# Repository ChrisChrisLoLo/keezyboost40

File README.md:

# keezyboost40

A 4x10 low profile ortholinear keyboard with an lcd screen in the center. Uses the Raspberry Pi Pico as well as firmware written in Rust (though QMK works too*)

## Features
- Low Profile
    - Keyboard is around 16.5mm thick, keys and keycaps included
- 1.8" LCD Screen
    - Ample real estate for animations, UI, games(?), etc.
- Uses the Raspberry Pi Pico
    - 2MB of flash storage
        - Lots of room for programming with MicroPython, or room for graphics and code
- Parts readily available
    - Only SMD parts required are diodes and kailh choc hotswap sockets
- Supports QMK or Rust firmware
    - QMK hex can be found in firmware file
    - Uses Keyberon as the firmware base, allowing for a "modular" firmware that can easily be built upon
    - More details can be found in DESIGN.md

Display demo here:

## Status
Prototypes are functional, though firmware is still WIP! v0.0 needs a jumper cable from the Pico to the reset pin in the TFT, but works perfectly fine with the Raspberry Pi Pico aside from that. v0.1 fixes this issue (currently in the `master` branch), though hasn't been produced and tested yet.

I need to fix a bug with the animation slowing down, though I suspect it'll mostly involve tinkering with RTOS timings

## PCB
You can generate the gerbers from source in the `pcb` directory, and send off imediately to PCBWay or the like. [PCBWay](https://www.pcbway.com/) has helped sponsor this project, and has provided a fast, easy service while ordering from them. I was also suprised how well my board came out desipte being quite oddly shaped, so I recommend checking them out for your next project!

## BOM
The following is the materials you will want/need to make your own keezyboost40. Note that anything amount after a `+` denotes the rough amount of spares you may want to have when ordering the parts. Anything involving the acrylic screen is optional. Even the LCD is optional if you prefer more of a lumberjack-y vibe :)
|Part|Count|Notes
|---|---|---|
|PCB|  1|   duh|
|Kailh Choc Hotswap Switches| 40+10| |
|LL4148 SMD Diodes|  40+10| This board uses SMD diodes exclusively. I found though-hole diodes often easily slipped around in a way such that the board was no longer able to fit inside the case|
|1.8" ST7735 TFT|  1| Generally speaking, you want the one with the Red PCB. Do NOT use the one from Adafruit, as the pin order on that one is different|
|Raspberry Pi Pico|  1| Try to get the original or a _very_ similar clone with castellated pins. From casual testing, other RP2040 boards may not work (for example, the Pico clones from WeAct can't seem to properly drive the LCD with 3.3V logic)|
|Rubber Feet|  6+2| Any should generally work, though I'm using ~2.5mm thick ones, as they give more space for screw heads, as well as the magnetic connector I'm using|
|3D Printed Case|  1| You could use PCB printing services like PCBWay to make one in resin, though I haven't confirmed if they'd be durable enough to survive in transit|
|M2 Nuts|  10+5| 6 nuts to hold the PCB to the case, and another 4 to hold the acrylic screen to the PCB. I'm using nylon nuts, though any should work. I recommend you grab this with a hex spacer kit, as you get all the M2 parts you need in a single purchase!|
|M2 8mm Double Female spacer|  4+2| Spacers to keep the acrylic from the pcb|
|M2 12mm Screw|  4+2| Screws for the acrylic screen|
|M2 6mm Screw|  6+3| Screws for the PCB and case. Be careful of the size of the screw head! the flatter the better!|
|Acrylic Screen|  1| You can cut one out using the svgs in the `outlines` folder|

## Design
See `DESIGN.md` for small insights about the design choices that went into this board. 

## Directory Structure
- `case`
    You can find the files you need in this folder to print out a case for the keyboard
- `drafts`
    Stores any KLE or intermediate information used in making the case
- `firmware`
    Used to store any firmware relating to the keyboard. Merges to the QMK repo planned.
- `outlines`
    Outlines used for the acrylic screen. Use these to cut your own!
- `pcb`
    Kicad project relating to the project

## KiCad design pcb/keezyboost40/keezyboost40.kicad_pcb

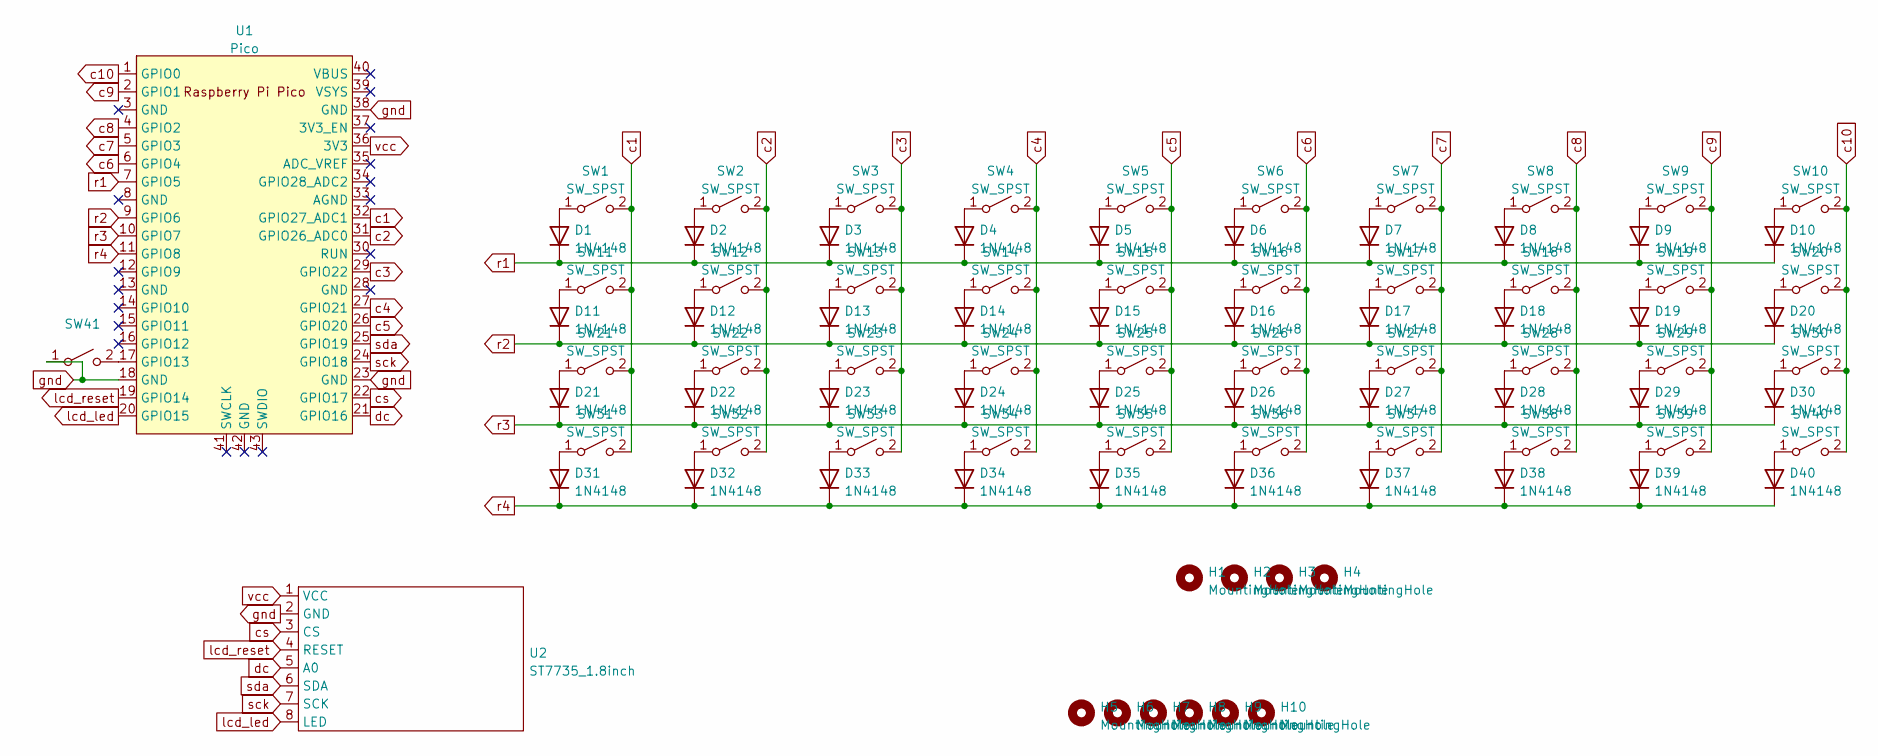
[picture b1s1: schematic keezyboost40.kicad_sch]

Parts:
D1, D2, D3, D4, D5, D6, D7, D8, D9, D10, D11, D12, D13, D14, D15, D16, D17, D18, D19, D20, D21, D22, D23, D24, D25, D26, D27, D28, D29, D30, D31, D32, D33, D34, D35, D36, D37, D38, D39, D40: 1N4148; D_SOD-123
H1, H2, H3, H4: MountingHole; MountingHole_2.2mm_M2_DIN965_Pad
H5, H6, H7, H8, H9, H10: MountingHole; MountingHole_2.2mm_M2
SW1, SW2, SW3, SW4, SW5, SW6, SW7, SW8, SW9, SW10, SW11, SW12, SW13, SW14, SW15, SW16, SW17, SW18, SW19, SW20, SW21, SW22, SW23, SW24, SW25, SW26, SW27, SW28, SW29, SW30, SW31, SW32, SW33, SW34, SW35, SW36, SW37, SW38, SW39, SW40: SW_SPST; Kailh_socket_PG1350
SW41: (no value)
U1: Pico; RPi_Pico_SMD_TH_OPEN
U2: ST7735_1.8inch

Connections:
unnamed: D1.2 (A), SW1.1 (A)
unnamed: D2.2 (A), SW2.1 (A)
unnamed: D3.2 (A), SW3.1 (A)
unnamed: D4.2 (A), SW4.1 (A)
unnamed: D5.2 (A), SW5.1 (A)
unnamed: D6.2 (A), SW6.1 (A)
unnamed: D7.2 (A), SW7.1 (A)
unnamed: D8.2 (A), SW8.1 (A)
unnamed: D9.2 (A), SW9.1 (A)
unnamed: D10.2 (A), SW10.1 (A)
unnamed: D11.2 (A), SW11.1 (A)
unnamed: D12.2 (A), SW12.1 (A)
unnamed: D13.2 (A), SW13.1 (A)
unnamed: D14.2 (A), SW14.1 (A)
unnamed: D15.2 (A), SW15.1 (A)
unnamed: D16.2 (A), SW16.1 (A)
unnamed: D17.2 (A), SW17.1 (A)
unnamed: D18.2 (A), SW18.1 (A)
unnamed: D19.2 (A), SW19.1 (A)
unnamed: D20.2 (A), SW20.1 (A)
unnamed: D21.2 (A), SW21.1 (A)
unnamed: D22.2 (A), SW22.1 (A)
unnamed: D23.2 (A), SW23.1 (A)
unnamed: D24.2 (A), SW24.1 (A)
unnamed: D25.2 (A), SW25.1 (A)
unnamed: D26.2 (A), SW26.1 (A)
unnamed: D27.2 (A), SW27.1 (A)
unnamed: D28.2 (A), SW28.1 (A)
unnamed: D29.2 (A), SW29.1 (A)
unnamed: D30.2 (A), SW30.1 (A)
unnamed: D31.2 (A), SW31.1 (A)
unnamed: D32.2 (A), SW32.1 (A)
unnamed: D33.2 (A), SW33.1 (A)
unnamed: D34.2 (A), SW34.1 (A)
unnamed: D35.2 (A), SW35.1 (A)
unnamed: D36.2 (A), SW36.1 (A)
unnamed: D37.2 (A), SW37.1 (A)
unnamed: D38.2 (A), SW38.1 (A)
unnamed: D39.2 (A), SW39.1 (A)
unnamed: D40.2 (A), SW40.1 (A)
unnamed: SW41.2 (B), U1.17 (GPIO13)
c1: SW1.2 (B), SW11.2 (B), SW21.2 (B), SW31.2 (B), U1.32 (GPIO27_ADC1)
c2: SW2.2 (B), SW12.2 (B), SW22.2 (B), SW32.2 (B), U1.31 (GPIO26_ADC0)
c3: SW3.2 (B), SW13.2 (B), SW23.2 (B), SW33.2 (B), U1.29 (GPIO22)
c4: SW4.2 (B), SW14.2 (B), SW24.2 (B), SW34.2 (B), U1.27 (GPIO21)
c5: SW5.2 (B), SW15.2 (B), SW25.2 (B), SW35.2 (B), U1.26 (GPIO20)
c6: SW6.2 (B), SW16.2 (B), SW26.2 (B), SW36.2 (B), U1.6 (GPIO4)
c7: SW7.2 (B), SW17.2 (B), SW27.2 (B), SW37.2 (B), U1.5 (GPIO3)
c8: SW8.2 (B), SW18.2 (B), SW28.2 (B), SW38.2 (B), U1.4 (GPIO2)
c9: SW9.2 (B), SW19.2 (B), SW29.2 (B), SW39.2 (B), U1.2 (GPIO1)
c10: SW10.2 (B), SW20.2 (B), SW30.2 (B), SW40.2 (B), U1.1 (GPIO0)
cs: U1.22 (GPIO17), U2.3 (CS)
dc: U1.21 (GPIO16), U2.5 (A0)
gnd: SW41.1 (A), U1.18 (GND), U1.23 (GND), U1.38 (GND), U2.2 (GND)
lcd_led: U1.20 (GPIO15), U2.8 (LED)
lcd_reset: U1.19 (GPIO14), U2.4 (RESET)
r1: D1.1 (K), D2.1 (K), D3.1 (K), D4.1 (K), D5.1 (K), D6.1 (K), D7.1 (K), D8.1 (K), D9.1 (K), D10.1 (K), U1.7 (GPIO5)
r2: D11.1 (K), D12.1 (K), D13.1 (K), D14.1 (K), D15.1 (K), D16.1 (K), D17.1 (K), D18.1 (K), D19.1 (K), D20.1 (K), U1.9 (GPIO6)
r3: D21.1 (K), D22.1 (K), D23.1 (K), D24.1 (K), D25.1 (K), D26.1 (K), D27.1 (K), D28.1 (K), D29.1 (K), D30.1 (K), U1.10 (GPIO7)
r4: D31.1 (K), D32.1 (K), D33.1 (K), D34.1 (K), D35.1 (K), D36.1 (K), D37.1 (K), D38.1 (K), D39.1 (K), D40.1 (K), U1.11 (GPIO8)
sck: U1.24 (GPIO18), U2.7 (SCK)
sda: U1.25 (GPIO19), U2.6 (SDA)
vcc: U1.36 (3V3), U2.1 (VCC)

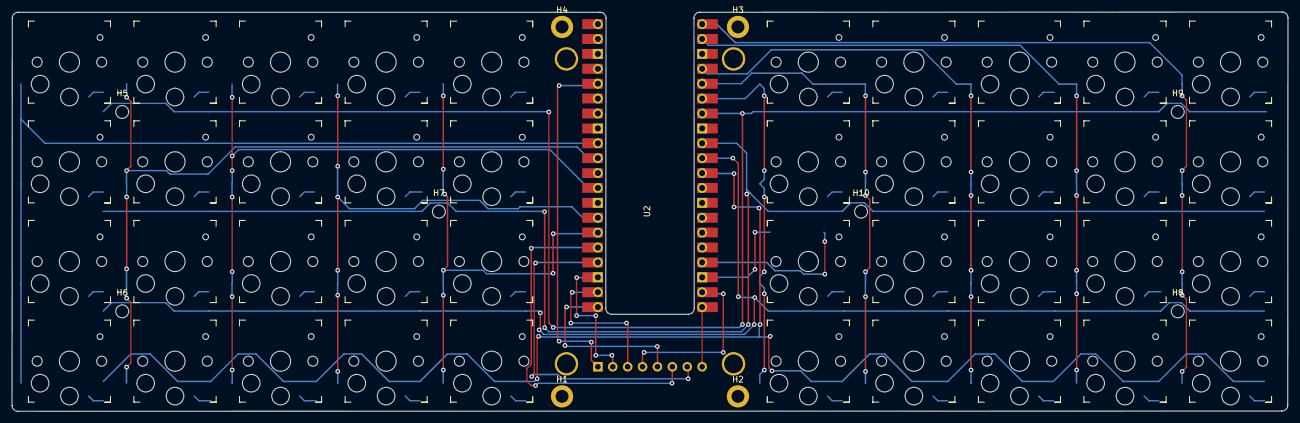
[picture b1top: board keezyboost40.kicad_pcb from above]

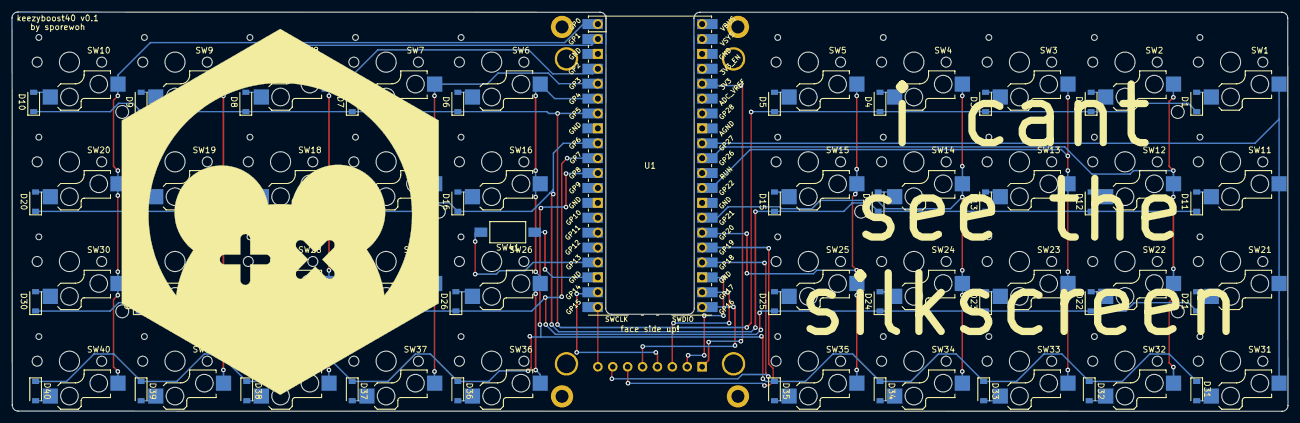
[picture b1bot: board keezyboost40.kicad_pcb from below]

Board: 2 copper layers, 217.6 x 68.1 mm, 93 parts (42 on the bottom side), 63 nets.

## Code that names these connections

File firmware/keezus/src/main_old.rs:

// Base taken from https://github.com/bschwind/key-ripper/blob/main/firmware/src/main.rs

#![no_main]
#![no_std]



use core::convert::Infallible;
use cortex_m::delay::Delay;
use defmt::{error, info};
use defmt_rtt as _;
use embedded_hal::{
    digital::v2::{InputPin, OutputPin},
    timer::CountDown,
};
use embedded_time::duration::Extensions;
// use panic_reset as _;
use panic_probe as _;
use rp2040_hal::{pac, usb::UsbBus, Clock, Watchdog};
use usb_device::{bus::UsbBusAllocator, device::UsbDeviceBuilder, prelude::UsbVidPid, UsbError};
use usbd_hid::{
    descriptor::KeyboardReport,
    hid_class::{
        HIDClass, HidClassSettings, HidCountryCode, HidProtocol, HidSubClass, ProtocolModeConfig,
    },
};

// lcd traits
use embedded_graphics::image::{Image, ImageRaw, ImageRawLE};
use embedded_graphics::prelude::*;
use embedded_graphics::pixelcolor::Rgb565;
use st7735_lcd;
use st7735_lcd::Orientation;
use embedded_time::rate::Hertz;

/// The linker will place this boot block at the start of our program image. We
/// need this to help the ROM bootloader get our code up and running.
#[link_section = ".boot2"]
#[used]
pub static BOOT2: [u8; 256] = rp2040_boot2::BOOT_LOADER_W25Q080;

mod hid_descriptor;
mod key_codes;
mod key_mapping;

const NUM_COLS: usize = 14;
const NUM_ROWS: usize = 6;

const EXTERNAL_CRYSTAL_FREQUENCY_HZ: u32 = 12_000_000;

#[defmt::panic_handler]
fn panic() -> ! {
    cortex_m::asm::udf()
}

#[cortex_m_rt::entry]
fn main() -> ! {
    info!("Start of main()");
    let mut pac = pac::Peripherals::take().unwrap();
    let core = pac::CorePeripherals::take().unwrap();

    let mut watchdog = Watchdog::new(pac.WATCHDOG);

    let clocks = rp2040_hal::clocks::init_clocks_and_plls(
        EXTERNAL_CRYSTAL_FREQUENCY_HZ,
        pac.XOSC,
        pac.CLOCKS,
        pac.PLL_SYS,
        pac.PLL_USB,
        &mut pac.RESETS,
        &mut watchdog,
    )
    .ok()
    .unwrap();

    // Setup USB
    let force_vbus_detect_bit = true;
    let usb_bus = UsbBus::new(
        pac.USBCTRL_REGS,
        pac.USBCTRL_DPRAM,
        clocks.usb_clock,
        force_vbus_detect_bit,
        &mut pac.RESETS,
    );

    let bus_allocator = UsbBusAllocator::new(usb_bus);

    // Note - Going lower than this requires switch debouncing.
    let poll_ms = 8;
    let mut hid_endpoint = HIDClass::new_with_settings(
        &bus_allocator,
        hid_descriptor::KEYBOARD_REPORT_DESCRIPTOR,
        poll_ms,
        HidClassSettings {
            subclass: HidSubClass::NoSubClass,
            protocol: HidProtocol::Keyboard,
            config: ProtocolModeConfig::ForceReport,
            // locale: HidCountryCode::NotSupported,
            locale: HidCountryCode::US,
        },
    );

    info!("USB initialized");

    // https://github.com/obdev/v-usb/blob/7a28fdc685952412dad2b8842429127bc1cf9fa7/usbdrv/USB-IDs-for-free.txt#L128
    let mut keyboard_usb_device = UsbDeviceBuilder::new(&bus_allocator, UsbVidPid(0x16c0, 0x27db))
        .manufacturer("bschwind")
        .product("key ripper")
        .build();

    // Get the GPIO peripherals.
    let sio = rp2040_hal::Sio::new(pac.SIO);

    let pins =
        rp2040_hal::gpio::Pins::new(pac.IO_BANK0, pac.PADS_BANK0, sio.gpio_bank0, &mut pac.RESETS);

    // Set up keyboard matrix pins.
    let rows: &[&dyn InputPin<Error = Infallible>] = &[
        &pins.gpio5.into_pull_down_input(),
        &pins.gpio6.into_pull_down_input(),
        &pins.gpio7.into_pull_down_input(),
        &pins.gpio8.into_pull_down_input(),
    ];

    let cols: &mut [&mut dyn OutputPin<Error = Infallible>] = &mut [
        &mut pins.gpio27.into_push_pull_output(),
        &mut pins.gpio26.into_push_pull_output(),
        &mut pins.gpio22.into_push_pull_output(),
        &mut pins.gpio21.into_push_pull_output(),
        &mut pins.gpio20.into_push_pull_output(),
        &mut pins.gpio4.into_push_pull_output(),
        &mut pins.gpio3.into_push_pull_output(),
        &mut pins.gpio2.into_push_pull_output(),
        &mut pins.gpio1.into_push_pull_output(),
        &mut pins.gpio0.into_push_pull_output(),
    ];

    // Timer-based resources.
    let mut delay = cortex_m::delay::Delay::new(core.SYST, clocks.system_clock.freq().0);

    let timer = rp2040_hal::Timer::new(pac.TIMER, &mut pac.RESETS);
    let mut scan_countdown = timer.count_down();

    // Start on a 500ms countdown so the USB endpoint writes don't block.
    scan_countdown.start(500.milliseconds());

    //// Start the TFT screen

    // These are implicitly used by the spi driver if they are in the correct mode
    let _spi_sclk = pins.gpio18.into_mode::<rp2040_hal::gpio::FunctionSpi>();
    let _spi_mosi = pins.gpio19.into_mode::<rp2040_hal::gpio::FunctionSpi>();
    //let _spi_miso = pins.gpio4.into_mode::<rp2040_hal::gpio::FunctionSpi>();
    let spi = rp2040_hal::Spi::<_, _, 8>::new(pac.SPI0);

    let mut lcd_led = pins.gpio15.into_push_pull_output();
    let dc = pins.gpio16.into_push_pull_output();
    let rst = pins.gpio14.into_push_pull_output();

    // Exchange the uninitialised SPI driver for an initialised one
    let spi = spi.init(
        &mut pac.RESETS,
        clocks.peripheral_clock.freq(),
        Hertz::new(16_000_000u32),
        &embedded_hal::spi::MODE_0,
    );


    let mut disp = st7735_lcd::ST7735::new(spi, dc, rst, true, false, 128, 160);

    disp.init(&mut delay).unwrap();
    disp.set_orientation(&Orientation::PortraitSwapped).unwrap();
    disp.clear(Rgb565::BLACK).unwrap();
    disp.set_offset(0, 25);

    let image_raw: ImageRawLE<Rgb565> =
        ImageRaw::new(include_bytes!("../assets/ferris.raw"), 86);

    let image: Image<_> = Image::new(&image_raw, Point::new(24, 28));

    image.draw(&mut disp).unwrap();
    
    // Wait until the background and image have been rendered otherwise
    // the screen will show random pixels for a brief moment
    lcd_led.set_high().unwrap();

    info!("Start main loop");

    // Main keyboard polling loop.
    loop {
        keyboard_usb_device.poll(&mut [&mut hid_endpoint]);

        if scan_countdown.wait().is_ok() {
            // Scan the keys and send a report.
            let matrix = scan_keys(rows, cols, &mut delay);
            let report = report_from_matrix(&matrix);

            match hid_endpoint.push_input(&report) {
                Ok(_) => {
                    scan_countdown.start(8.milliseconds());
                },
                Err(err) => match err {
                    UsbError::WouldBlock => info!("UsbError::WouldBlock"),
                    UsbError::ParseError => error!("UsbError::ParseError"),
                    UsbError::BufferOverflow => error!("UsbError::BufferOverflow"),
                    UsbError::EndpointOverflow => error!("UsbError::EndpointOverflow"),
                    UsbError::EndpointMemoryOverflow => error!("UsbError::EndpointMemoryOverflow"),
                    UsbError::InvalidEndpoint => error!("UsbError::InvalidEndpoint"),
                    UsbError::Unsupported => error!("UsbError::Unsupported"),
                    UsbError::InvalidState => error!("UsbError::InvalidState"),
                },
            }
        }

        hid_endpoint.pull_raw_output(&mut [0; 64]).ok();
    }
}

fn scan_keys(
    rows: &[&dyn InputPin<Error = Infallible>],
    columns: &mut [&mut dyn embedded_hal::digital::v2::OutputPin<Error = Infallible>],
    delay: &mut Delay,
) -> [[bool; NUM_ROWS]; NUM_COLS] {
    let mut matrix = [[false; NUM_ROWS]; NUM_COLS];

    for (gpio_col, matrix_col) in columns.iter_mut().zip(matrix.iter_mut()) {
        gpio_col.set_high().unwrap();
        delay.delay_us(10);

        for (gpio_row, matrix_row) in rows.iter().zip(matrix_col.iter_mut()) {
            *matrix_row = gpio_row.is_high().unwrap();
        }

        gpio_col.set_low().unwrap();
        delay.delay_us(10);
    }

    matrix
}

fn report_from_matrix(matrix: &[[bool; NUM_ROWS]; NUM_COLS]) -> KeyboardReport {
    let mut keycodes = [0u8; 6];
    let mut keycode_index = 0;
    let mut modifier = 0;

    let mut push_keycode = |key| {
        if keycode_index < keycodes.len() {
            keycodes[keycode_index] = key;
            keycode_index += 1;
        }
    };

    // let layer_mapping = if matrix[0][5] {
    //     key_mapping::FN_LAYER_MAPPING
    // } else {
    //     key_mapping::NORMAL_LAYER_MAPPING
    // };
    layer_mapping = key_mapping::NORMAL_LAYER_MAPPING;

    for (matrix_column, mapping_column) in matrix.iter().zip(layer_mapping) {
        for (key_pressed, mapping_row) in matrix_column.iter().zip(mapping_column) {
            if *key_pressed {
                if let Some(bitmask) = mapping_row.modifier_bitmask() {
                    modifier |= bitmask;
                } else {
                    push_keycode(mapping_row as u8);
                }
            }
        }
    }

    KeyboardReport { modifier, reserved: 0, leds: 0, keycodes }
}

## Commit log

2022-07-09 init commit
2022-07-10 add initial tft lcd footprint
2022-07-10 start adding lcd
2022-07-10 update outlines
2022-07-12 finish v0.0
2022-07-15 create gerbers
2022-07-16 fixup issues with lcd interface connections
2022-07-17 init commit for rust firmware
2022-07-17 add lcd library
2022-07-22 update firmware
2022-07-23 make lcd use 3.3v over 5v
2022-08-03 add sheild outlines
2022-08-06 KEEZUS IS ONLINE
2022-08-06 begin adding display
2022-08-07 update interrupts
2022-08-07 Fix screen display by moving watchdog initialization to the end (BAD DOG >:()
2022-08-08 fix "ghosting" issue: pull from local fork
2022-08-10 add basic screen animation
2022-08-12 Add docs
2022-08-12 Update docs
2022-08-12 fix typo
2022-08-12 add case files
2022-08-12 add readmes
2022-08-21 update sponsor info and change 6mm spacer to 8mm spacer
2022-09-05 use keyberon fork with patched matrix scanning delay
2022-10-08 add reset button
2022-12-19 Update GitHub path
2024-04-13 Add a case with a bigger cutout
